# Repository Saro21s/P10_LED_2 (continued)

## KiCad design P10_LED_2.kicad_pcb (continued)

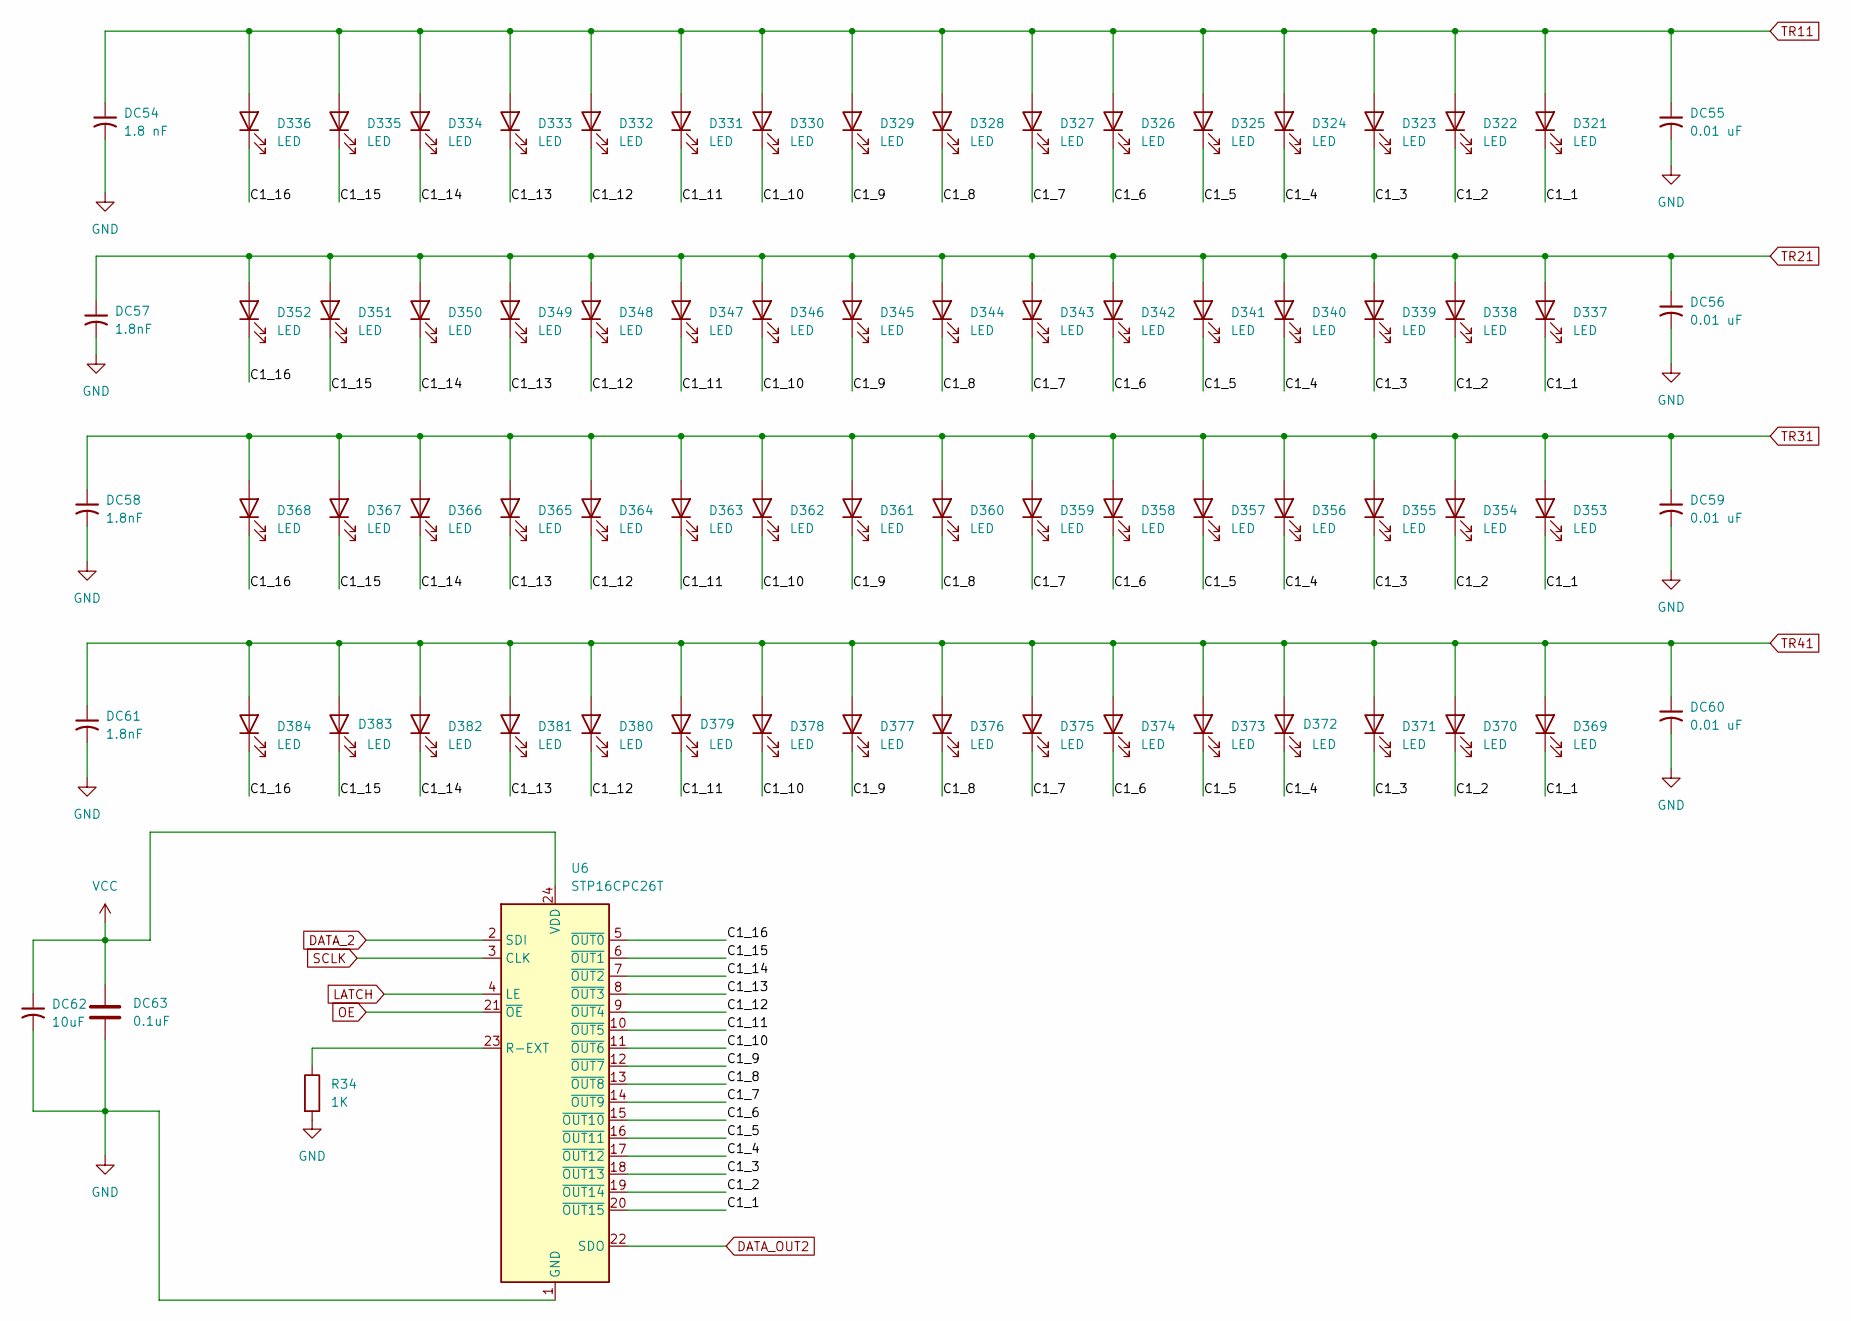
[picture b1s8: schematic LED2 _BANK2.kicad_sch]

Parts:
D321, D322, D323, D324, D325, D326, D327, D328, D329, D330, D331, D332, D333, D334, D335, D336, D337, D338, D339, D340, D341, D342, D343, D344, D345, D346, D347, D348, D349, D350, D351, D352, D353, D354, D355, D356, D357, D358, D359, D360, D361, D362, D363, D364, D365, D366, D367, D368, D369, D370, D371, D372, D373, D374, D375, D376, D377, D378, D379, D380, D381, D382, D383, D384: LED; LED_0805_2012Metric
DC54: 1.8 nF; C_0805_2012Metric
DC55, DC56, DC59, DC60: 0.01 uF; C_0805_2012Metric
DC57, DC58, DC61: 1.8nF; C_0805_2012Metric
DC62: 10uF; C_0805_2012Metric
DC63: 0.1uF; C_0805_2012Metric
R34: 1K; R_0805_2012Metric
U6: STP16CPC26T; TSSOP-24_4.4x7.8mm_P0.65mm

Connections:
/LED2_BANK2/C1_1: D321.1 (K), D337.1 (K), D353.1 (K), D369.1 (K), U6.20 (~OUT15)
/LED2_BANK2/C1_2: D322.1 (K), D338.1 (K), D354.1 (K), D370.1 (K), U6.19 (~OUT14)
/LED2_BANK2/C1_3: D323.1 (K), D339.1 (K), D355.1 (K), D371.1 (K), U6.18 (~OUT13)
/LED2_BANK2/C1_4: D324.1 (K), D340.1 (K), D356.1 (K), D372.1 (K), U6.17 (~OUT12)
/LED2_BANK2/C1_5: D325.1 (K), D341.1 (K), D357.1 (K), D373.1 (K), U6.16 (~OUT11)
/LED2_BANK2/C1_6: D326.1 (K), D342.1 (K), D358.1 (K), D374.1 (K), U6.15 (~OUT10)
/LED2_BANK2/C1_7: D327.1 (K), D343.1 (K), D359.1 (K), D375.1 (K), U6.14 (~OUT9)
/LED2_BANK2/C1_8: D328.1 (K), D344.1 (K), D360.1 (K), D376.1 (K), U6.13 (~OUT8)
/LED2_BANK2/C1_9: D329.1 (K), D345.1 (K), D361.1 (K), D377.1 (K), U6.12 (~OUT7)
/LED2_BANK2/C1_10: D330.1 (K), D346.1 (K), D362.1 (K), D378.1 (K), U6.11 (~OUT6)
/LED2_BANK2/C1_11: D331.1 (K), D347.1 (K), D363.1 (K), D379.1 (K), U6.10 (~OUT5)
/LED2_BANK2/C1_12: D332.1 (K), D348.1 (K), D364.1 (K), D380.1 (K), U6.9 (~OUT4)
/LED2_BANK2/C1_13: D333.1 (K), D349.1 (K), D365.1 (K), D381.1 (K), U6.8 (~OUT3)
/LED2_BANK2/C1_14: D334.1 (K), D350.1 (K), D366.1 (K), D382.1 (K), U6.7 (~OUT2)
/LED2_BANK2/C1_15: D335.1 (K), D351.1 (K), D367.1 (K), D383.1 (K), U6.6 (~OUT1)
/LED2_BANK2/C1_16: D336.1 (K), D352.1 (K), D368.1 (K), D384.1 (K), U6.5 (~OUT0)
DATA_2: U6.2 (SDI); also elsewhere on the board
DATA_OUT2: U6.22 (SDO); also elsewhere on the board
GND: DC54.2, DC55.2, DC56.2, DC57.2, DC58.2, DC59.2, DC60.2, DC61.2, DC62.2, DC63.2, R34.2, U6.1 (GND); also elsewhere on the board
LATCH: U6.4 (LE); also elsewhere on the board
unnamed: R34.1, U6.23 (R-EXT)
OE: U6.21 (~OE); also elsewhere on the board
SCLK: U6.3 (CLK); also elsewhere on the board
TR11: D321.2 (A), D322.2 (A), D323.2 (A), D324.2 (A), D325.2 (A), D326.2 (A), D327.2 (A), D328.2 (A), D329.2 (A), D330.2 (A), D331.2 (A), D332.2 (A), D333.2 (A), D334.2 (A), D335.2 (A), D336.2 (A), DC54.1, DC55.1; also elsewhere on the board
TR21: D337.2 (A), D338.2 (A), D339.2 (A), D340.2 (A), D341.2 (A), D342.2 (A), D343.2 (A), D344.2 (A), D345.2 (A), D346.2 (A), D347.2 (A), D348.2 (A), D349.2 (A), D350.2 (A), D351.2 (A), D352.2 (A), DC56.1, DC57.1; also elsewhere on the board
TR31: D353.2 (A), D354.2 (A), D355.2 (A), D356.2 (A), D357.2 (A), D358.2 (A), D359.2 (A), D360.2 (A), D361.2 (A), D362.2 (A), D363.2 (A), D364.2 (A), D365.2 (A), D366.2 (A), D367.2 (A), D368.2 (A), DC58.1, DC59.1; also elsewhere on the board
TR41: D369.2 (A), D370.2 (A), D371.2 (A), D372.2 (A), D373.2 (A), D374.2 (A), D375.2 (A), D376.2 (A), D377.2 (A), D378.2 (A), D379.2 (A), D380.2 (A), D381.2 (A), D382.2 (A), D383.2 (A), D384.2 (A), DC60.1, DC61.1; also elsewhere on the board
VCC: DC62.1, DC63.1, U6.24 (VDD); also elsewhere on the board

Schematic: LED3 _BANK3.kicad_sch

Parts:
D385, D386, D387, D388, D389, D390, D391, D392, D393, D394, D395, D396, D397, D398, D399, D400, D401, D402, D403, D404, D405, D406, D407, D408, D409, D410, D411, D412, D413, D414, D415, D416, D417, D418, D419, D420, D421, D422, D423, D424, D425, D426, D427, D428, D429, D430, D431, D432, D433, D434, D435, D436, D437, D438, D439, D440, D441, D442, D443, D444, D445, D446, D447, D448: LED; LED_0805_2012Metric
DC64, DC67, DC68, DC71: 1.8 nF; C_0805_2012Metric
DC65, DC66, DC69, DC70: 0.01 uF; C_0805_2012Metric
DC72: 10uF; C_0805_2012Metric
DC73: 0.1uF; C_0805_2012Metric
R35: 1K; R_0805_2012Metric
U7: STP16CPC26T; TSSOP-24_4.4x7.8mm_P0.65mm

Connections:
/LED3 _BANK3/C1_1: D385.1 (K), D401.1 (K), D417.1 (K), D433.1 (K), U7.20 (~OUT15)
/LED3 _BANK3/C1_2: D386.1 (K), D402.1 (K), D418.1 (K), D434.1 (K), U7.19 (~OUT14)
/LED3 _BANK3/C1_3: D387.1 (K), D403.1 (K), D419.1 (K), D435.1 (K), U7.18 (~OUT13)
/LED3 _BANK3/C1_4: D388.1 (K), D404.1 (K), D420.1 (K), D436.1 (K), U7.17 (~OUT12)
/LED3 _BANK3/C1_5: D389.1 (K), D405.1 (K), D421.1 (K), D437.1 (K), U7.16 (~OUT11)
/LED3 _BANK3/C1_6: D390.1 (K), D406.1 (K), D422.1 (K), D438.1 (K), U7.15 (~OUT10)
/LED3 _BANK3/C1_7: D391.1 (K), D407.1 (K), D423.1 (K), D439.1 (K), U7.14 (~OUT9)
/LED3 _BANK3/C1_8: D392.1 (K), D408.1 (K), D424.1 (K), D440.1 (K), U7.13 (~OUT8)
/LED3 _BANK3/C1_9: D393.1 (K), D409.1 (K), D425.1 (K), D441.1 (K), U7.12 (~OUT7)
/LED3 _BANK3/C1_10: D394.1 (K), D410.1 (K), D426.1 (K), D442.1 (K), U7.11 (~OUT6)
/LED3 _BANK3/C1_11: D395.1 (K), D411.1 (K), D427.1 (K), D443.1 (K), U7.10 (~OUT5)
/LED3 _BANK3/C1_12: D396.1 (K), D412.1 (K), D428.1 (K), D444.1 (K), U7.9 (~OUT4)
/LED3 _BANK3/C1_13: D397.1 (K), D413.1 (K), D429.1 (K), D445.1 (K), U7.8 (~OUT3)
/LED3 _BANK3/C1_14: D398.1 (K), D414.1 (K), D430.1 (K), D446.1 (K), U7.7 (~OUT2)
/LED3 _BANK3/C1_15: D399.1 (K), D415.1 (K), D431.1 (K), D447.1 (K), U7.6 (~OUT1)
/LED3 _BANK3/C1_16: D400.1 (K), D416.1 (K), D432.1 (K), D448.1 (K), U7.5 (~OUT0)
DATA_3: U7.2 (SDI); also elsewhere on the board
DATA_OUT3: U7.22 (SDO); also elsewhere on the board
GND: DC64.2, DC65.2, DC66.2, DC67.2, DC68.2, DC69.2, DC70.2, DC71.2, DC72.2, DC73.2, R35.2, U7.1 (GND); also elsewhere on the board
LATCH: U7.4 (LE); also elsewhere on the board
unnamed: R35.1, U7.23 (R-EXT)
OE: U7.21 (~OE); also elsewhere on the board
SCLK: U7.3 (CLK); also elsewhere on the board
TR11: D385.2 (A), D386.2 (A), D387.2 (A), D388.2 (A), D389.2 (A), D390.2 (A), D391.2 (A), D392.2 (A), D393.2 (A), D394.2 (A), D395.2 (A), D396.2 (A), D397.2 (A), D398.2 (A), D399.2 (A), D400.2 (A), DC64.1, DC65.1; also elsewhere on the board
TR21: D401.2 (A), D402.2 (A), D403.2 (A), D404.2 (A), D405.2 (A), D406.2 (A), D407.2 (A), D408.2 (A), D409.2 (A), D410.2 (A), D411.2 (A), D412.2 (A), D413.2 (A), D414.2 (A), D415.2 (A), D416.2 (A), DC66.1, DC67.1; also elsewhere on the board
TR31: D417.2 (A), D418.2 (A), D419.2 (A), D420.2 (A), D421.2 (A), D422.2 (A), D423.2 (A), D424.2 (A), D425.2 (A), D426.2 (A), D427.2 (A), D428.2 (A), D429.2 (A), D430.2 (A), D431.2 (A), D432.2 (A), DC68.1, DC69.1; also elsewhere on the board
TR41: D433.2 (A), D434.2 (A), D435.2 (A), D436.2 (A), D437.2 (A), D438.2 (A), D439.2 (A), D440.2 (A), D441.2 (A), D442.2 (A), D443.2 (A), D444.2 (A), D445.2 (A), D446.2 (A), D447.2 (A), D448.2 (A), DC70.1, DC71.1; also elsewhere on the board
VCC: DC72.1, DC73.1, U7.24 (VDD); also elsewhere on the board

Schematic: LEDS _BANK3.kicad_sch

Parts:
D129, D130, D131, D132, D133, D134, D135, D136, D137, D138, D139, D140, D141, D142, D143, D144, D145, D146, D147, D148, D149, D150, D151, D152, D153, D154, D155, D156, D157, D158, D159, D160, D161, D162, D163, D164, D165, D166, D167, D168, D169, D170, D171, D172, D173, D174, D175, D176, D177, D178, D179, D180, D181, D182, D183, D184, D185, D186, D187, D188, D189, D190, D191, D192: LED; LED_0805_2012Metric
DC24: 10uF; C_0805_2012Metric
DC25: 1.8 nF; C_0805_2012Metric
DC26, DC27, DC31, DC32: 0.01 uF; C_0805_2012Metric
DC28, DC30, DC33: 1.8nF; C_0805_2012Metric
DC29: 0.1uF; C_0805_2012Metric
R31: 1K; R_0805_2012Metric
U3: STP16CPC26T; TSSOP-24_4.4x7.8mm_P0.65mm

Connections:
/LEDS _BANK3/C1_1: D129.1 (K), D145.1 (K), D161.1 (K), D177.1 (K), U3.20 (~OUT15)
/LEDS _BANK3/C1_2: D130.1 (K), D146.1 (K), D162.1 (K), D178.1 (K), U3.19 (~OUT14)
/LEDS _BANK3/C1_3: D131.1 (K), D147.1 (K), D163.1 (K), D179.1 (K), U3.18 (~OUT13)
/LEDS _BANK3/C1_4: D132.1 (K), D148.1 (K), D164.1 (K), D180.1 (K), U3.17 (~OUT12)
/LEDS _BANK3/C1_5: D133.1 (K), D149.1 (K), D165.1 (K), D181.1 (K), U3.16 (~OUT11)
/LEDS _BANK3/C1_6: D134.1 (K), D150.1 (K), D166.1 (K), D182.1 (K), U3.15 (~OUT10)
/LEDS _BANK3/C1_7: D135.1 (K), D151.1 (K), D167.1 (K), D183.1 (K), U3.14 (~OUT9)
/LEDS _BANK3/C1_8: D136.1 (K), D152.1 (K), D168.1 (K), D184.1 (K), U3.13 (~OUT8)
/LEDS _BANK3/C1_9: D137.1 (K), D153.1 (K), D169.1 (K), D185.1 (K), U3.12 (~OUT7)
/LEDS _BANK3/C1_10: D138.1 (K), D154.1 (K), D170.1 (K), D186.1 (K), U3.11 (~OUT6)
/LEDS _BANK3/C1_11: D139.1 (K), D155.1 (K), D171.1 (K), D187.1 (K), U3.10 (~OUT5)
/LEDS _BANK3/C1_12: D140.1 (K), D156.1 (K), D172.1 (K), D188.1 (K), U3.9 (~OUT4)
/LEDS _BANK3/C1_13: D141.1 (K), D157.1 (K), D173.1 (K), D189.1 (K), U3.8 (~OUT3)
/LEDS _BANK3/C1_14: D142.1 (K), D158.1 (K), D174.1 (K), D190.1 (K), U3.7 (~OUT2)
/LEDS _BANK3/C1_15: D143.1 (K), D159.1 (K), D175.1 (K), D191.1 (K), U3.6 (~OUT1)
/LEDS _BANK3/C1_16: D144.1 (K), D160.1 (K), D176.1 (K), D192.1 (K), U3.5 (~OUT0)
DATA_3: U3.22 (SDO); also elsewhere on the board
DATA_3_IN: U3.2 (SDI); also elsewhere on the board
GND: DC24.2, DC25.2, DC26.2, DC27.2, DC28.2, DC29.2, DC30.2, DC31.2, DC32.2, DC33.2, R31.2, U3.1 (GND); also elsewhere on the board
LATCH: U3.4 (LE); also elsewhere on the board
unnamed: R31.1, U3.23 (R-EXT)
OE: U3.21 (~OE); also elsewhere on the board
SCLK: U3.3 (CLK); also elsewhere on the board
TR11: D129.2 (A), D130.2 (A), D131.2 (A), D132.2 (A), D133.2 (A), D134.2 (A), D135.2 (A), D136.2 (A), D137.2 (A), D138.2 (A), D139.2 (A), D140.2 (A), D141.2 (A), D142.2 (A), D143.2 (A), D144.2 (A), DC25.1, DC26.1; also elsewhere on the board
TR21: D145.2 (A), D146.2 (A), D147.2 (A), D148.2 (A), D149.2 (A), D150.2 (A), D151.2 (A), D152.2 (A), D153.2 (A), D154.2 (A), D155.2 (A), D156.2 (A), D157.2 (A), D158.2 (A), D159.2 (A), D160.2 (A), DC27.1, DC28.1; also elsewhere on the board
TR31: D161.2 (A), D162.2 (A), D163.2 (A), D164.2 (A), D165.2 (A), D166.2 (A), D167.2 (A), D168.2 (A), D169.2 (A), D170.2 (A), D171.2 (A), D172.2 (A), D173.2 (A), D174.2 (A), D175.2 (A), D176.2 (A), DC30.1, DC31.1; also elsewhere on the board
TR41: D177.2 (A), D178.2 (A), D179.2 (A), D180.2 (A), D181.2 (A), D182.2 (A), D183.2 (A), D184.2 (A), D185.2 (A), D186.2 (A), D187.2 (A), D188.2 (A), D189.2 (A), D190.2 (A), D191.2 (A), D192.2 (A), DC32.1, DC33.1; also elsewhere on the board
VCC: DC24.1, DC29.1, U3.24 (VDD); also elsewhere on the board

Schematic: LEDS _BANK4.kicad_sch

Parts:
D193, D194, D195, D196, D197, D198, D199, D200, D201, D202, D203, D204, D205, D206, D207, D208, D209, D210, D211, D212, D213, D214, D215, D216, D217, D218, D219, D220, D221, D222, D223, D224, D225, D226, D227, D228, D229, D230, D231, D232, D233, D234, D235, D236, D237, D238, D239, D240, D241, D242, D243, D244, D245, D246, D247, D248, D249, D250, D251, D252, D253, D254, D255, D256: LED; LED_0805_2012Metric
DC34: 1.8 nF; C_0805_2012Metric
DC35, DC36, DC39, DC40: 0.01 uF; C_0805_2012Metric
DC37, DC38, DC41: 1.8nF; C_0805_2012Metric
DC42: 10uF; C_0805_2012Metric
DC43: 0.1uF; C_0805_2012Metric
R32: 1K; R_0805_2012Metric
U4: STP16CPC26T; TSSOP-24_4.4x7.8mm_P0.65mm

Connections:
/LEDS _BANK4 (page 11)/C1_1: D193.1 (K), D209.1 (K), D225.1 (K), D241.1 (K), U4.20 (~OUT15)
/LEDS _BANK4 (page 11)/C1_2: D194.1 (K), D210.1 (K), D226.1 (K), D242.1 (K), U4.19 (~OUT14)
/LEDS _BANK4 (page 11)/C1_3: D195.1 (K), D211.1 (K), D227.1 (K), D243.1 (K), U4.18 (~OUT13)
/LEDS _BANK4 (page 11)/C1_4: D196.1 (K), D212.1 (K), D228.1 (K), D244.1 (K), U4.17 (~OUT12)
/LEDS _BANK4 (page 11)/C1_5: D197.1 (K), D213.1 (K), D229.1 (K), D245.1 (K), U4.16 (~OUT11)
/LEDS _BANK4 (page 11)/C1_6: D198.1 (K), D214.1 (K), D230.1 (K), D246.1 (K), U4.15 (~OUT10)
/LEDS _BANK4 (page 11)/C1_7: D199.1 (K), D215.1 (K), D231.1 (K), D247.1 (K), U4.14 (~OUT9)
/LEDS _BANK4 (page 11)/C1_8: D200.1 (K), D216.1 (K), D232.1 (K), D248.1 (K), U4.13 (~OUT8)
/LEDS _BANK4 (page 11)/C1_9: D201.1 (K), D217.1 (K), D233.1 (K), D249.1 (K), U4.12 (~OUT7)
/LEDS _BANK4 (page 11)/C1_10: D202.1 (K), D218.1 (K), D234.1 (K), D250.1 (K), U4.11 (~OUT6)
/LEDS _BANK4 (page 11)/C1_11: D203.1 (K), D219.1 (K), D235.1 (K), D251.1 (K), U4.10 (~OUT5)
/LEDS _BANK4 (page 11)/C1_12: D204.1 (K), D220.1 (K), D236.1 (K), D252.1 (K), U4.9 (~OUT4)
/LEDS _BANK4 (page 11)/C1_13: D205.1 (K), D221.1 (K), D237.1 (K), D253.1 (K), U4.8 (~OUT3)
/LEDS _BANK4 (page 11)/C1_14: D206.1 (K), D222.1 (K), D238.1 (K), D254.1 (K), U4.7 (~OUT2)
/LEDS _BANK4 (page 11)/C1_15: D207.1 (K), D223.1 (K), D239.1 (K), D255.1 (K), U4.6 (~OUT1)
/LEDS _BANK4 (page 11)/C1_16: D208.1 (K), D224.1 (K), D240.1 (K), D256.1 (K), U4.5 (~OUT0)
DATA_4: U4.22 (SDO); also elsewhere on the board
DATA_4_IN: U4.2 (SDI); also elsewhere on the board
GND: DC34.2, DC35.2, DC36.2, DC37.2, DC38.2, DC39.2, DC40.2, DC41.2, DC42.2, DC43.2, R32.2, U4.1 (GND); also elsewhere on the board
LATCH: U4.4 (LE); also elsewhere on the board
unnamed: R32.1, U4.23 (R-EXT)
OE: U4.21 (~OE); also elsewhere on the board
SCLK: U4.3 (CLK); also elsewhere on the board
TR11: D193.2 (A), D194.2 (A), D195.2 (A), D196.2 (A), D197.2 (A), D198.2 (A), D199.2 (A), D200.2 (A), D201.2 (A), D202.2 (A), D203.2 (A), D204.2 (A), D205.2 (A), D206.2 (A), D207.2 (A), D208.2 (A), DC34.1, DC35.1; also elsewhere on the board
TR21: D209.2 (A), D210.2 (A), D211.2 (A), D212.2 (A), D213.2 (A), D214.2 (A), D215.2 (A), D216.2 (A), D217.2 (A), D218.2 (A), D219.2 (A), D220.2 (A), D221.2 (A), D222.2 (A), D223.2 (A), D224.2 (A), DC36.1, DC37.1; also elsewhere on the board
TR31: D225.2 (A), D226.2 (A), D227.2 (A), D228.2 (A), D229.2 (A), D230.2 (A), D231.2 (A), D232.2 (A), D233.2 (A), D234.2 (A), D235.2 (A), D236.2 (A), D237.2 (A), D238.2 (A), D239.2 (A), D240.2 (A), DC38.1, DC39.1; also elsewhere on the board
TR41: D241.2 (A), D242.2 (A), D243.2 (A), D244.2 (A), D245.2 (A), D246.2 (A), D247.2 (A), D248.2 (A), D249.2 (A), D250.2 (A), D251.2 (A), D252.2 (A), D253.2 (A), D254.2 (A), D255.2 (A), D256.2 (A), DC40.1, DC41.1; also elsewhere on the board
VCC: DC42.1, DC43.1, U4.24 (VDD); also elsewhere on the board

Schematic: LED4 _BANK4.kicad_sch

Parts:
D449, D450, D451, D452, D453, D454, D455, D456, D457, D458, D459, D460, D461, D462, D463, D464, D465, D466, D467, D468, D469, D470, D471, D472, D473, D474, D475, D476, D477, D478, D479, D480, D481, D482, D483, D484, D485, D486, D487, D488, D489, D490, D491, D492, D493, D494, D495, D496, D497, D498, D499, D500, D501, D502, D503, D504, D505, D506, D507, D508, D509, D510, D511, D512: LED; LED_0805_2012Metric
DC74, DC77, DC78, DC81: 1.8 nF; C_0805_2012Metric
DC75, DC76, DC79, DC80: 0.01 uF; C_0805_2012Metric
DC82: 10uF; C_0805_2012Metric
DC83: 0.1uF; C_0805_2012Metric
R36: 1K; R_0805_2012Metric
U8: STP16CPC26T; TSSOP-24_4.4x7.8mm_P0.65mm

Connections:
/LED4 _BANK4/C1_1: D449.1 (K), D465.1 (K), D481.1 (K), D497.1 (K), U8.20 (~OUT15)
/LED4 _BANK4/C1_2: D450.1 (K), D466.1 (K), D482.1 (K), D498.1 (K), U8.19 (~OUT14)
/LED4 _BANK4/C1_3: D451.1 (K), D467.1 (K), D483.1 (K), D499.1 (K), U8.18 (~OUT13)
/LED4 _BANK4/C1_4: D452.1 (K), D468.1 (K), D484.1 (K), D500.1 (K), U8.17 (~OUT12)
/LED4 _BANK4/C1_5: D453.1 (K), D469.1 (K), D485.1 (K), D501.1 (K), U8.16 (~OUT11)
/LED4 _BANK4/C1_6: D454.1 (K), D470.1 (K), D486.1 (K), D502.1 (K), U8.15 (~OUT10)
/LED4 _BANK4/C1_7: D455.1 (K), D471.1 (K), D487.1 (K), D503.1 (K), U8.14 (~OUT9)
/LED4 _BANK4/C1_8: D456.1 (K), D472.1 (K), D488.1 (K), D504.1 (K), U8.13 (~OUT8)
/LED4 _BANK4/C1_9: D457.1 (K), D473.1 (K), D489.1 (K), D505.1 (K), U8.12 (~OUT7)
/LED4 _BANK4/C1_10: D458.1 (K), D474.1 (K), D490.1 (K), D506.1 (K), U8.11 (~OUT6)
/LED4 _BANK4/C1_11: D459.1 (K), D475.1 (K), D491.1 (K), D507.1 (K), U8.10 (~OUT5)
/LED4 _BANK4/C1_12: D460.1 (K), D476.1 (K), D492.1 (K), D508.1 (K), U8.9 (~OUT4)
/LED4 _BANK4/C1_13: D461.1 (K), D477.1 (K), D493.1 (K), D509.1 (K), U8.8 (~OUT3)
/LED4 _BANK4/C1_14: D462.1 (K), D478.1 (K), D494.1 (K), D510.1 (K), U8.7 (~OUT2)
/LED4 _BANK4/C1_15: D463.1 (K), D479.1 (K), D495.1 (K), D511.1 (K), U8.6 (~OUT1)
/LED4 _BANK4/C1_16: D464.1 (K), D480.1 (K), D496.1 (K), D512.1 (K), U8.5 (~OUT0)
DATA_4: U8.2 (SDI); also elsewhere on the board
DATA_OUT4: U8.22 (SDO); also elsewhere on the board
GND: DC74.2, DC75.2, DC76.2, DC77.2, DC78.2, DC79.2, DC80.2, DC81.2, DC82.2, DC83.2, R36.2, U8.1 (GND); also elsewhere on the board
LATCH: U8.4 (LE); also elsewhere on the board
unnamed: R36.1, U8.23 (R-EXT)
OE: U8.21 (~OE); also elsewhere on the board
SCLK: U8.3 (CLK); also elsewhere on the board
TR11: D449.2 (A), D450.2 (A), D451.2 (A), D452.2 (A), D453.2 (A), D454.2 (A), D455.2 (A), D456.2 (A), D457.2 (A), D458.2 (A), D459.2 (A), D460.2 (A), D461.2 (A), D462.2 (A), D463.2 (A), D464.2 (A), DC74.1, DC75.1; also elsewhere on the board
TR21: D465.2 (A), D466.2 (A), D467.2 (A), D468.2 (A), D469.2 (A), D470.2 (A), D471.2 (A), D472.2 (A), D473.2 (A), D474.2 (A), D475.2 (A), D476.2 (A), D477.2 (A), D478.2 (A), D479.2 (A), D480.2 (A), DC76.1, DC77.1; also elsewhere on the board
TR31: D481.2 (A), D482.2 (A), D483.2 (A), D484.2 (A), D485.2 (A), D486.2 (A), D487.2 (A), D488.2 (A), D489.2 (A), D490.2 (A), D491.2 (A), D492.2 (A), D493.2 (A), D494.2 (A), D495.2 (A), D496.2 (A), DC78.1, DC79.1; also elsewhere on the board
TR41: D497.2 (A), D498.2 (A), D499.2 (A), D500.2 (A), D501.2 (A), D502.2 (A), D503.2 (A), D504.2 (A), D505.2 (A), D506.2 (A), D507.2 (A), D508.2 (A), D509.2 (A), D510.2 (A), D511.2 (A), D512.2 (A), DC80.1, DC81.1; also elsewhere on the board
VCC: DC82.1, DC83.1, U8.24 (VDD); also elsewhere on the board

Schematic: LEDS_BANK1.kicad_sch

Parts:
D1, D2, D3, D4, D5, D6, D7, D8, D9, D10, D11, D12, D13, D14, D15, D16, D17, D18, D19, D20, D21, D22, D23, D24, D25, D26, D27, D28, D29, D30, D31, D32, D33, D34, D35, D36, D37, D38, D39, D40, D41, D42, D43, D44, D45, D46, D47, D48, D49, D50, D51, D52, D53, D54, D55, D56, D57, D58, D59, D60, D61, D62, D63, D64: LED; LED_0805_2012Metric
DC4: 1.8 nF; C_0805_2012Metric
DC5, DC6, DC9, DC10: 0.01 uF; C_0805_2012Metric
DC7, DC8, DC11: 1.8nf; C_0805_2012Metric
DC12: 10uF; C_0805_2012Metric
DC13: 0.1uF; C_0805_2012Metric
R29: 1K; R_0805_2012Metric
U1: STP16CPC26T; TSSOP-24_4.4x7.8mm_P0.65mm

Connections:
/LEDS_BANK1/C1_1: D1.1 (K), D17.1 (K), D33.1 (K), D49.1 (K), U1.20 (~OUT15)
/LEDS_BANK1/C1_2: D2.1 (K), D18.1 (K), D34.1 (K), D50.1 (K), U1.19 (~OUT14)
/LEDS_BANK1/C1_3: D3.1 (K), D19.1 (K), D35.1 (K), D51.1 (K), U1.18 (~OUT13)
/LEDS_BANK1/C1_4: D4.1 (K), D20.1 (K), D36.1 (K), D52.1 (K), U1.17 (~OUT12)
/LEDS_BANK1/C1_5: D5.1 (K), D21.1 (K), D37.1 (K), D53.1 (K), U1.16 (~OUT11)
/LEDS_BANK1/C1_6: D6.1 (K), D22.1 (K), D38.1 (K), D54.1 (K), U1.15 (~OUT10)
/LEDS_BANK1/C1_7: D7.1 (K), D23.1 (K), D39.1 (K), D55.1 (K), U1.14 (~OUT9)
/LEDS_BANK1/C1_8: D8.1 (K), D24.1 (K), D40.1 (K), D56.1 (K), U1.13 (~OUT8)
/LEDS_BANK1/C1_9: D9.1 (K), D25.1 (K), D41.1 (K), D57.1 (K), U1.12 (~OUT7)
/LEDS_BANK1/C1_10: D10.1 (K), D26.1 (K), D42.1 (K), D58.1 (K), U1.11 (~OUT6)
/LEDS_BANK1/C1_11: D11.1 (K), D27.1 (K), D43.1 (K), D59.1 (K), U1.10 (~OUT5)
/LEDS_BANK1/C1_12: D12.1 (K), D28.1 (K), D44.1 (K), D60.1 (K), U1.9 (~OUT4)
/LEDS_BANK1/C1_13: D13.1 (K), D29.1 (K), D45.1 (K), D61.1 (K), U1.8 (~OUT3)
/LEDS_BANK1/C1_14: D14.1 (K), D30.1 (K), D46.1 (K), D62.1 (K), U1.7 (~OUT2)
/LEDS_BANK1/C1_15: D15.1 (K), D31.1 (K), D47.1 (K), D63.1 (K), U1.6 (~OUT1)
/LEDS_BANK1/C1_16: D16.1 (K), D32.1 (K), D48.1 (K), D64.1 (K), U1.5 (~OUT0)
DATA_1: U1.22 (SDO); also elsewhere on the board
DATA_1_IN: U1.2 (SDI); also elsewhere on the board
GND: DC4.2, DC5.2, DC6.2, DC7.2, DC8.2, DC9.2, DC10.2, DC11.2, DC12.2, DC13.2, R29.2, U1.1 (GND); also elsewhere on the board
LATCH: U1.4 (LE); also elsewhere on the board
unnamed: R29.1, U1.23 (R-EXT)
OE: U1.21 (~OE); also elsewhere on the board
SCLK: U1.3 (CLK); also elsewhere on the board
TR11: D1.2 (A), D2.2 (A), D3.2 (A), D4.2 (A), D5.2 (A), D6.2 (A), D7.2 (A), D8.2 (A), D9.2 (A), D10.2 (A), D11.2 (A), D12.2 (A), D13.2 (A), D14.2 (A), D15.2 (A), D16.2 (A), DC4.1, DC5.1; also elsewhere on the board
TR21: D17.2 (A), D18.2 (A), D19.2 (A), D20.2 (A), D21.2 (A), D22.2 (A), D23.2 (A), D24.2 (A), D25.2 (A), D26.2 (A), D27.2 (A), D28.2 (A), D29.2 (A), D30.2 (A), D31.2 (A), D32.2 (A), DC6.1, DC7.1; also elsewhere on the board
TR31: D33.2 (A), D34.2 (A), D35.2 (A), D36.2 (A), D37.2 (A), D38.2 (A), D39.2 (A), D40.2 (A), D41.2 (A), D42.2 (A), D43.2 (A), D44.2 (A), D45.2 (A), D46.2 (A), D47.2 (A), D48.2 (A), DC8.1, DC9.1; also elsewhere on the board
TR41: D49.2 (A), D50.2 (A), D51.2 (A), D52.2 (A), D53.2 (A), D54.2 (A), D55.2 (A), D56.2 (A), D57.2 (A), D58.2 (A), D59.2 (A), D60.2 (A), D61.2 (A), D62.2 (A), D63.2 (A), D64.2 (A), DC10.1, DC11.1; also elsewhere on the board
VCC: DC12.1, DC13.1, U1.24 (VDD); also elsewhere on the board

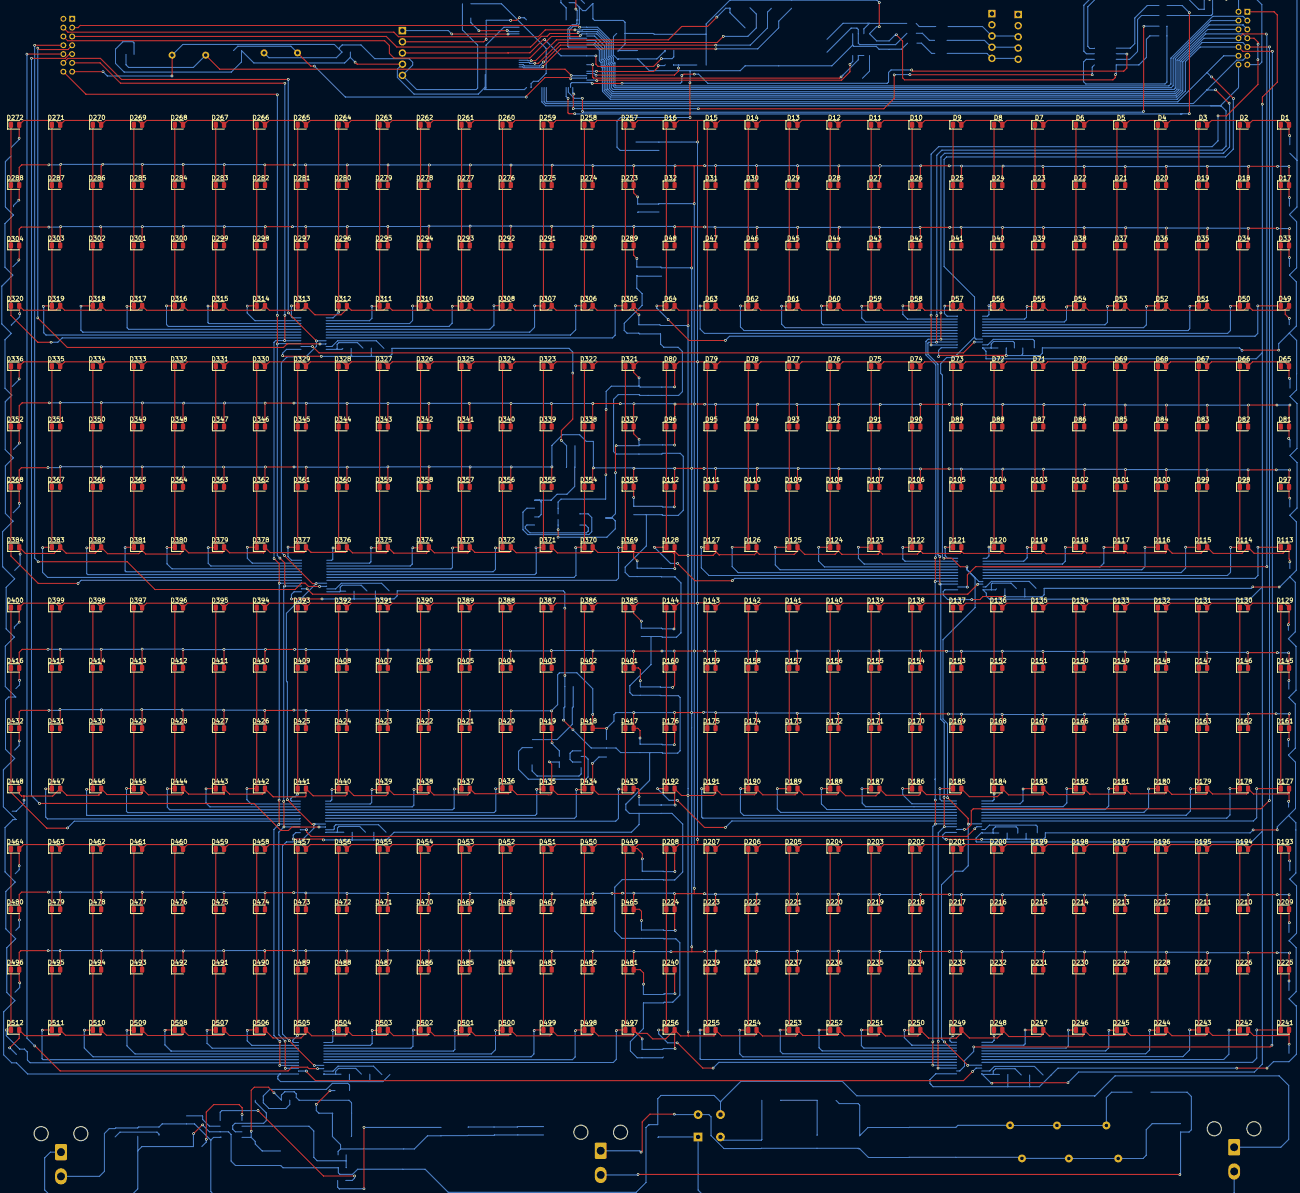
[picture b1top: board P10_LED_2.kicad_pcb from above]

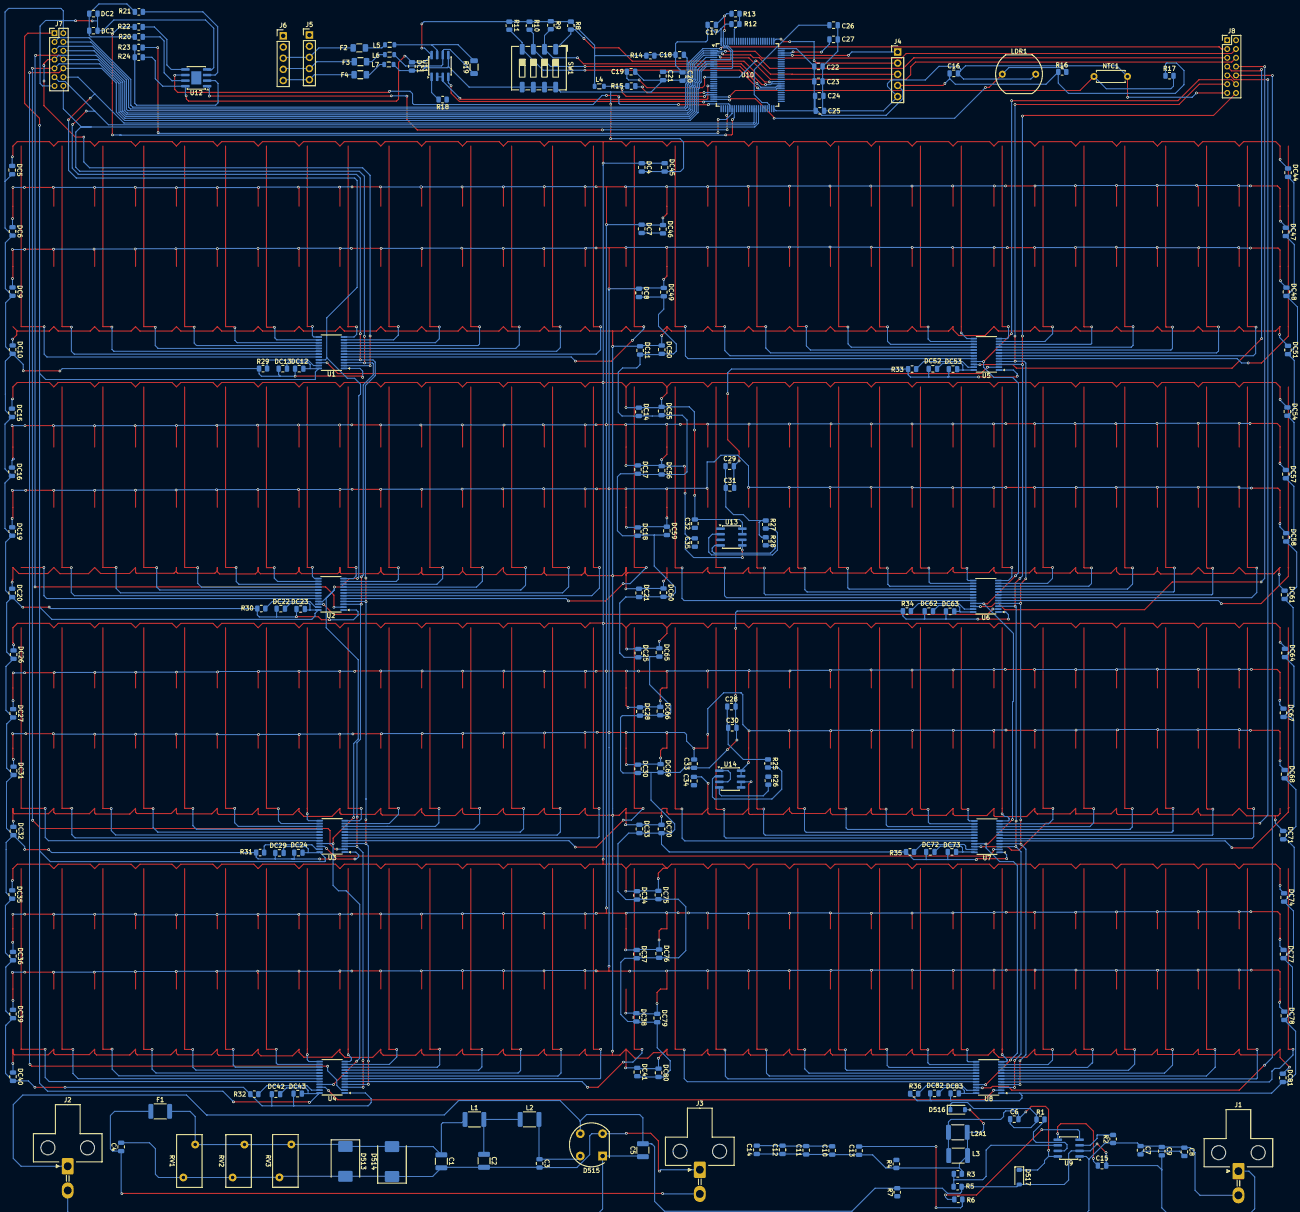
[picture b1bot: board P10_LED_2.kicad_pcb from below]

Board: 2 copper layers, 711 parts (199 on the bottom side), 216 nets.

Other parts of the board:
C28: 10uF; C_0805_2012Metric
C29: 10 uF; C_0805_2012Metric
C30: 0.1uF; C_0805_2012Metric
C31: 0.1 uF; C_0805_2012Metric
C32: 0.01 uF; C_0805_2012Metric
C33, C34, C35: 0.01uF; C_0805_2012Metric
R25, R26, R27, R28: 4.7K; R_0805_2012Metric
U13, U14: SOIC-8_3.9x4.9mm_P1.27mm

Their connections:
GND: C28.2, C29.2, C30.2, C31.2, C32.1, C33.1, C34.2, C35.1; also elsewhere on the board
ROWA: R27.2, U13.2 (G1); also elsewhere on the board
ROWB: R28.2, U13.4 (G2); also elsewhere on the board
ROWC: R25.2, U14.2 (G1); also elsewhere on the board
ROWD: R26.2, U14.4 (G2); also elsewhere on the board
TR11: C32.2, U13.7 (D1.2), U13.8 (D1.1); also elsewhere on the board
TR21: C35.2, U13.5 (D2.2), U13.6 (D2.1); also elsewhere on the board
TR31: C33.2, U14.7 (D1.2), U14.8 (D1.1); also elsewhere on the board
TR41: C34.1, U14.5 (D2.2), U14.6 (D2.1); also elsewhere on the board
VCC_3V3_1: C29.1, C31.1, R27.1, R28.1; also elsewhere on the board
VCC_3V3_2: C28.1, C30.1, R25.1, R26.1
